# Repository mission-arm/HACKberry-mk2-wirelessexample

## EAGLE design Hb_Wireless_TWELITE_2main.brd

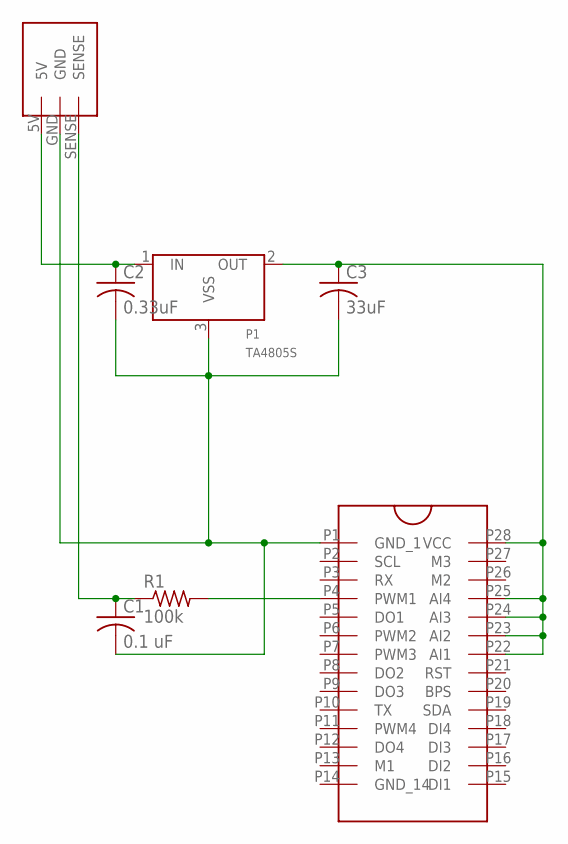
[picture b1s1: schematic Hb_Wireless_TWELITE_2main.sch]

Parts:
C1: 0.1 uF; C050-024X044
C2: 0.33uF; C050-024X044
C3: 33uF; C050-024X044
P1: TA4805S; TA48**S
R1: 100k; 0207/7
U$1: TWE-LITE-DIP
U$2: CON2MAIN

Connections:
unnamed: C1.2, C2.2, C3.2, P1.3 (VSS), U$1.P1 (GND_1), U$2.GND
unnamed: C3.1, P1.2 (OUT), U$1.P22 (AI1), U$1.P23 (AI2), U$1.P24 (AI3), U$1.P25 (AI4), U$1.P28 (VCC)
unnamed: C2.1, P1.1 (IN), U$2.5V
unnamed: C1.1, R1.1, U$2.SENSE
unnamed: R1.2, U$1.P4 (PWM1)

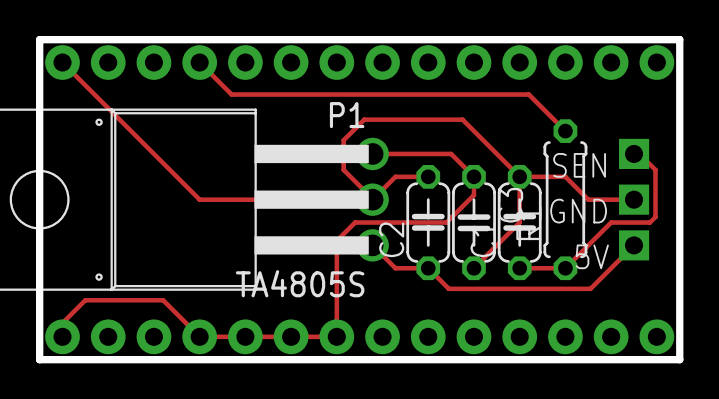
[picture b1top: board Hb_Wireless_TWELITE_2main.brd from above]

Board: 2 copper layers, 35.6 x 17.8 mm, 7 parts (1 on the bottom side), 5 nets.
